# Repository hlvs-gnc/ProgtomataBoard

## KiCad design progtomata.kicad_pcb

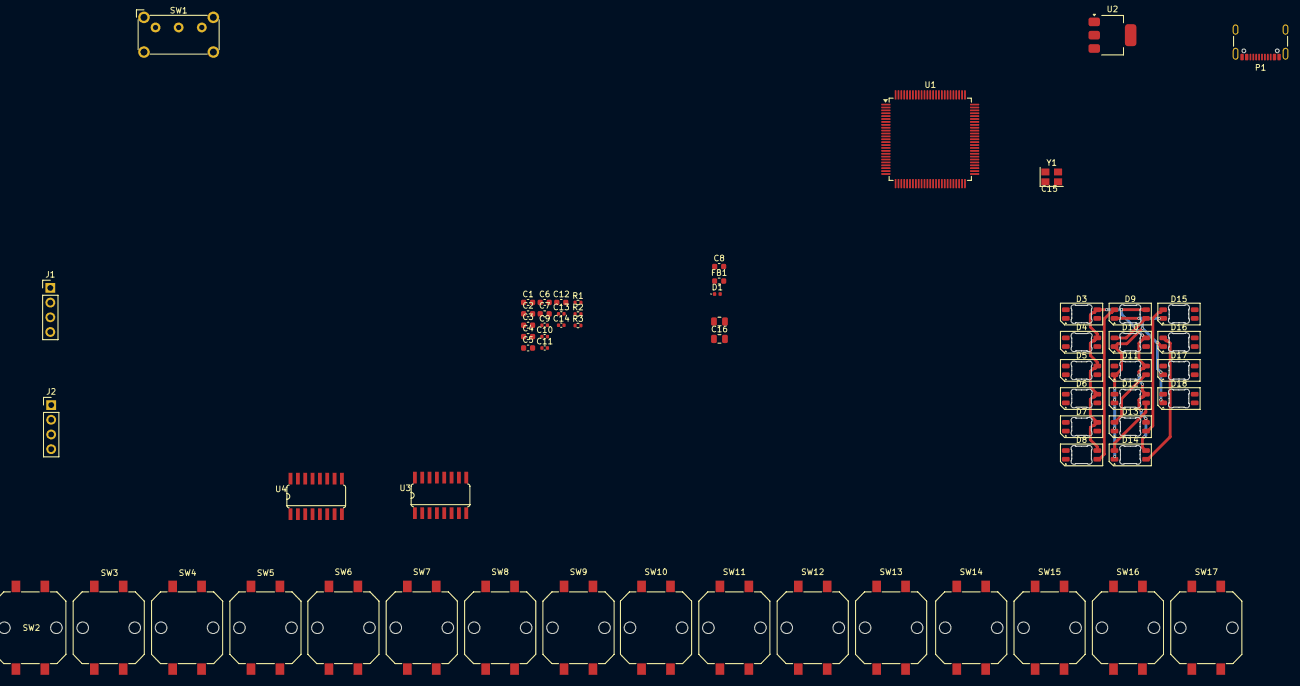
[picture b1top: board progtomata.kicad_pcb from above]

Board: 2 copper layers, 62 parts (0 on the bottom side), 53 nets.

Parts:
C1, C2, C3, C4, C5, C6, C7, C12: 100n; C_0603_1608Metric
C8: 10u; C_0603_1608Metric
C9: 10n; C_0402_1005Metric
C10, C11: 1u; C_0402_1005Metric
C13, C14: 10p; C_0402_1005Metric
C15, C16: 22u; C_0805_2012Metric
D1: GREEN; LED_0402_1005Metric
D3, D4, D5, D6, D7, D8, D9, D10, D11, D12, D13, D14, D15, D16, D17, D18: SK6812MINI-E; LED_SK6812MINI-E_3.2x2.8mm_P1.5mm_ReverseMount
FB1: 120R; L_0603_1608Metric
J1, J2: Conn_01x04_Pin; PinHeader_1x04_P2.54mm_Vertical
P1: USB_C_Plug_USB2.0; USB_C_Receptacle_GCT_USB4105-xx-A_16P_TopMnt_Horizontal
R1: 10k; R_0402_1005Metric
R2: 1k5; R_0402_1005Metric
R3: 5.1k; R_0402_1005Metric
SW1: SW_SPDT; SW_E-Switch_EG1224_SPDT_Angled
SW2, SW3, SW4, SW5, SW6, SW7, SW8, SW9, SW10, SW11, SW12, SW13, SW14, SW15, SW16, SW17: SW_Push; SW_Push_1P1T_NO_CK_PTS125Sx43PSMTR
U1: STM32F407VGTx; LQFP-100_14x14mm_P0.5mm
U2: AMS1117-3.3; SOT-223-3_TabPin2
U3, U4: 74LS148; SO16
Y1: 8MHz; Crystal_SMD_3225-4Pin_3.2x2.5mm

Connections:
+5V: C1.1, C2.1, C3.1, C4.1, C5.1, C6.1, C7.1, C8.1, C9.1, C10.1, C11.1, C16.1, D1.2 (A), D3.3 (VDD), D4.3 (VDD), D5.3 (VDD), D6.3 (VDD), D7.3 (VDD), D8.3 (VDD), D9.3 (VDD), D10.3 (VDD), D11.3 (VDD), D12.3 (VDD), D13.3 (VDD), D14.3 (VDD), D15.3 (VDD), D16.3 (VDD), D17.3 (VDD), D18.3 (VDD), FB1.1, FB1.2, J1.1, J2.1, SW1.3 (C), SW2.1, SW3.1, SW4.1, SW5.1, SW6.1, SW7.1, SW8.1, SW9.1, SW10.1, SW11.1, SW12.1, SW13.1, SW14.1, SW15.1, SW16.1, SW17.1, U1.6 (VBAT), U1.11 (VDD), U1.19 (VDD), U1.22 (VDDA), U1.28 (VDD), U1.50 (VDD), U1.75 (VDD), U1.100 (VDD), U2.2 (VO), U3.16 (VCC), U4.16 (VCC)
/BOOT0: R1.2, U1.94 (BOOT0)
/HSE_IN: C13.1, U1.12 (PH0), Y1.1
/HSE_OUT: C14.1, U1.13 (PH1), Y1.3
/LED_I1: D6.4 (DOUT), D7.2 (DIN)
/LED_I2: D10.4 (DOUT), D11.2 (DIN)
/LED_K1: D12.2 (DIN), D17.4 (DOUT)
/NRST: C12.1, U1.14 (NRST)
/PWR_LED_K: D1.1 (K), R2.1
/SW_BOOT0: R1.1, SW1.2 (B)
/USB_D+: P1.A6 (D+), U1.71 (PA12)
/USB_D-: P1.A7 (D-), U1.70 (PA11)
ENC1_I0: SW2.2, U3.10 (IO)
ENC1_I1: SW3.2, U3.11 (I1)
ENC1_I2: SW4.2, U3.12 (I2)
ENC1_I3: SW5.2, U3.13 (I3)
ENC1_I4: SW6.2, U3.1 (I4)
ENC1_I5: SW7.2, U3.2 (I5)
ENC1_I6: SW8.2, U3.3 (I6)
ENC1_I7: SW9.2, U3.4 (I7)
ENC1_Q0: U1.97 (PE0), U3.9 (S0)
ENC1_Q1: U1.98 (PE1), U3.7 (S1)
ENC1_Q2: U1.1 (PE2), U3.6 (S2)
ENC2_I0: SW10.2, U4.10 (IO)
ENC2_I1: SW11.2, U4.11 (I1)
ENC2_I2: SW12.2, U4.12 (I2)
ENC2_I3: SW13.2, U4.13 (I3)
ENC2_I4: SW14.2, U4.1 (I4)
ENC2_I5: SW15.2, U4.2 (I5)
ENC2_I6: SW16.2, U4.3 (I6)
ENC2_I7: SW17.2, U4.4 (I7)
ENC2_Q0: U1.7 (PC13), U4.9 (S0)
ENC2_Q1: U1.8 (PC14), U4.7 (S1)
ENC2_Q2: U1.9 (PC15), U4.6 (S2)
GND: C1.2, C2.2, C3.2, C4.2, C5.2, C6.2, C7.2, C8.2, C9.2, C10.2, C11.2, C12.2, C13.2, C14.2, C15.2, C16.2, D3.1 (VSS), D4.1 (VSS), D5.1 (VSS), D6.1 (VSS), D7.1 (VSS), D8.1 (VSS), D9.1 (VSS), D10.1 (VSS), D11.1 (VSS), D12.1 (VSS), D13.1 (VSS), D14.1 (VSS), D15.1 (VSS), D16.1 (VSS), D17.1 (VSS), D18.1 (VSS), J1.4, J2.4, P1.A1 (GND), P1.A12 (GND), P1.B1 (GND), P1.B12 (GND), R2.2, R3.2, SW1.1 (A), U1.10 (VSS), U1.20 (VSSA), U1.27 (VSS), U1.74 (VSS), U1.99 (VSS), U2.1 (GND), U3.8 (GND), U4.8 (GND), Y1.2, Y1.4
unnamed: D3.4 (DOUT), D4.2 (DIN)
unnamed: D4.4 (DOUT), D5.2 (DIN)
unnamed: D5.4 (DOUT), D6.2 (DIN)
unnamed: D7.4 (DOUT), D8.2 (DIN)
unnamed: D8.4 (DOUT), D9.2 (DIN)
unnamed: D9.4 (DOUT), D10.2 (DIN)
unnamed: D11.4 (DOUT), D13.2 (DIN)
unnamed: D12.4 (DOUT), D14.2 (DIN)
unnamed: D13.4 (DOUT), D15.2 (DIN)
unnamed: D14.4 (DOUT), D16.2 (DIN)
unnamed: D15.4 (DOUT), D17.2 (DIN)
unnamed: D16.4 (DOUT), D18.2 (DIN)
unnamed: P1.A5 (CC), R3.1
SWCLK: J1.3, U1.76 (PA14)
SWDIO: J1.2, U1.72 (PA13)
UART_RX: J2.2, U1.25 (PA2)
UART_TX: J2.3, U1.26 (PA3)
VBUS: C15.1, P1.A4 (VBUS), P1.A9 (VBUS), P1.B4 (VBUS), P1.B9 (VBUS), U2.3 (VI)

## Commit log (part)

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2025-07-17 Update schematics
2025-07-17 Add 8-bit priority encoder
2025-07-18 Change priority encoder footprint
2025-07-18 Update PCB footprint (USB-C port, button priority encoder)
2025-07-21 Add button interface
